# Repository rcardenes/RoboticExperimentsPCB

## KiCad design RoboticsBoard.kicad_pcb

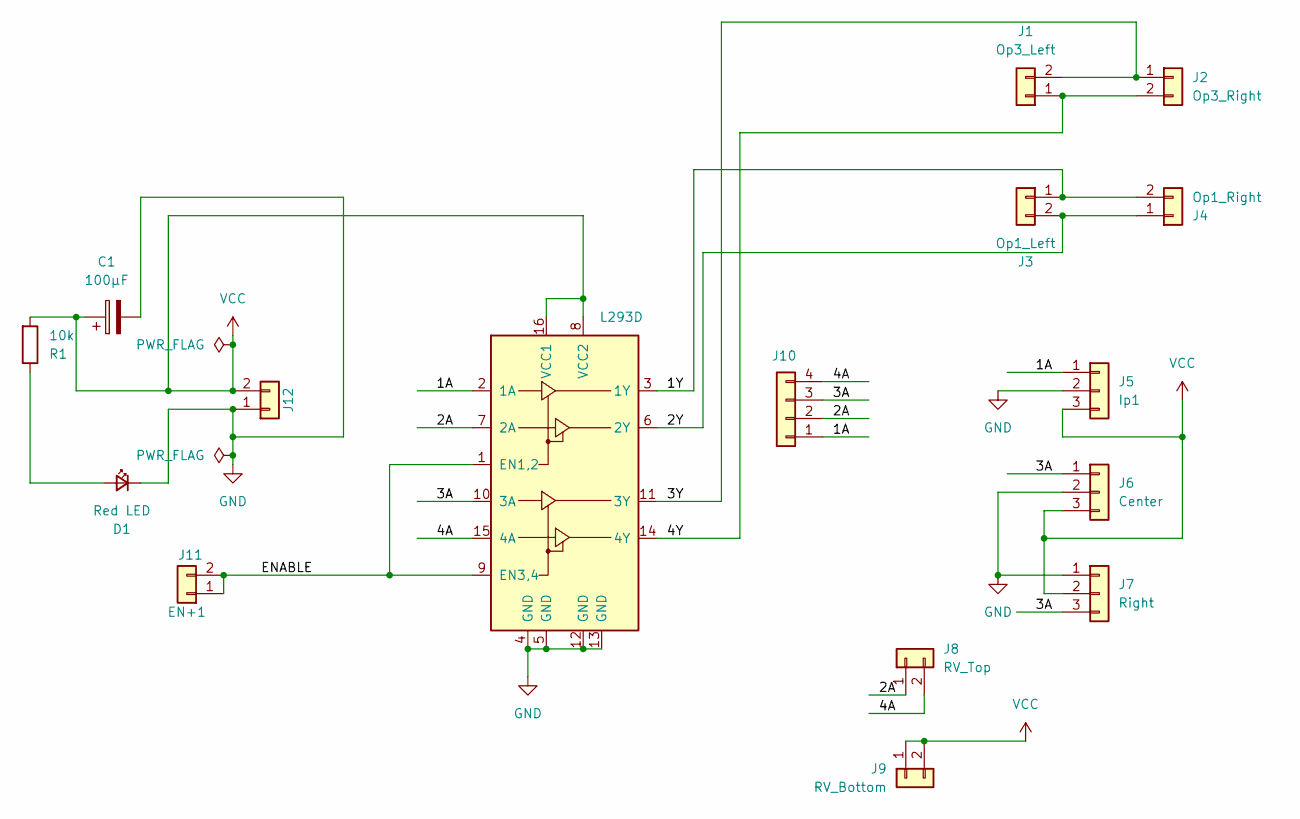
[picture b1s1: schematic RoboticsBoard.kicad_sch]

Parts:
C1: 100µF; CP_Radial_D4.0mm_P2.00mm
D1: Red LED; LED_D3.0mm
J1: Op3_Left; PinHeader_2x01_P2.00mm_Vertical
J2: Op3_Right; PinHeader_2x01_P2.00mm_Vertical
J3: Op1_Left; PinHeader_2x01_P2.00mm_Vertical
J4: Op1_Right; PinHeader_2x01_P2.00mm_Vertical
J5: Ip1; PinHeader_1x03_P2.00mm_Vertical
J6: Center; PinHeader_1x03_P2.00mm_Vertical
J7: Right; PinHeader_1x03_P2.00mm_Vertical
J8: RV_Top; PinHeader_2x01_P2.00mm_Vertical
J9: RV_Bottom; PinHeader_2x01_P2.00mm_Vertical
J10: IP/MOTOR; PinHeader_1x04_P2.00mm_Vertical
J11: EN+1; PinHeader_2x01_P2.00mm_Vertical
J12: Power; PinHeader_2x01_P2.00mm_Vertical
R1: 10k; R_Axial_DIN0204_L3.6mm_D1.6mm_P7.62mm_Horizontal
U1: L293D; DIP-16_W7.62mm_Socket

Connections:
/1A: J5.1, J10.1 (IN1), U1.2 (1A)
/1Y: J3.1, J4.2, U1.3 (1Y)
/2A: J8.1, J10.2 (IN2), U1.7 (2A)
/2Y: J3.2, J4.1, U1.6 (2Y)
/3A: J6.1, J7.3, J10.3 (IN3), U1.10 (3A)
/3Y: J1.2, J2.1, U1.11 (3Y)
/4A: J8.2, J10.4 (IN4), U1.15 (4A)
/4Y: J1.1, J2.2, U1.14 (4Y)
/ENABLE: J11.1, J11.2, U1.1 (EN1,2), U1.9 (EN3,4)
GND: C1.2, D1.1 (K), J5.2, J6.2, J7.1, J12.1, U1.4 (GND), U1.5 (GND), U1.12 (GND), U1.13 (GND)
unnamed: D1.2 (A), R1.1
VCC: C1.1, J5.3, J6.3, J7.2, J9.1, J9.2, J12.2, R1.2, U1.8 (VCC2), U1.16 (VCC1)

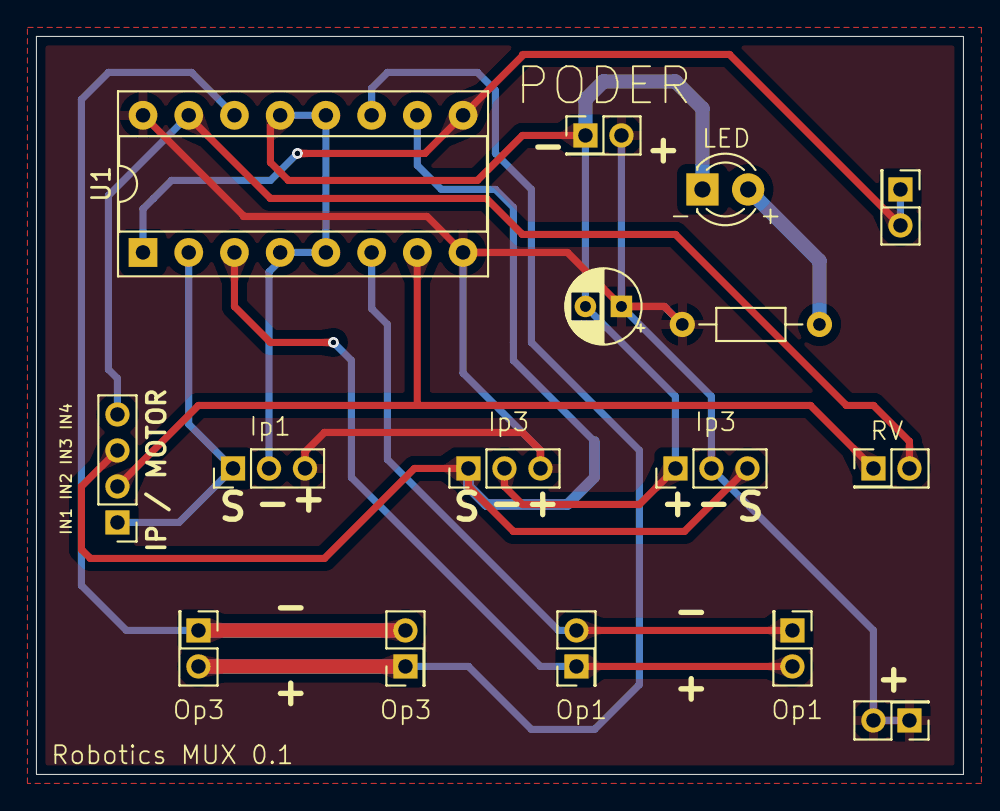
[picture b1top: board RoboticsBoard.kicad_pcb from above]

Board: 2 copper layers, 51.5 x 41.0 mm, 16 parts (0 on the bottom side), 12 nets.

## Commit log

2024-04-16 First iteration - capture the original design
